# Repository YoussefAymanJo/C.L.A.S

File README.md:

# C.L.A.S

## Description
Is an abbreviation for a closed-loop feedback system.A system that monitors and acts based on lettuce & pepper plant conditions in 6th October city,Egypt.
In  monitors temperature & Humidty & soil moiture & light intensity.then,it responds in case in change in plants optimal range conditonns.As,it used actuctors,peltiers ,humidifier,heating lamp ,grow light , water pump and fan to out excessive humidty.It powered by esp s3.and cloud base storage of firebase,show data at moment on web app.
## Why it was built
This is grade 11 Capstone Project in my school,so i must make it.It is about the challenge Egypt faces in integrating IoT closed systems with farming.My project solve this by providing high nutrition needed crops in my area all the year,lettuce&pepper controlled  by closed feedback system.that control temperature & humidty & soil moisture & light parameters.
## How to use it / Build it
 First of all,prepare materials ,then buy wood and start cut into blocks,after that open parts in wood using cnc for actuactors and other in pcb enclosure.After that assemble all together using nails and wood glue.then adding electronic compontes sesnor & actucators.and connect them first to power supply to test it.then connect each one alone first to esp ,then test them all.after that,check wire isolation and system working and real data from sesnors.test system manul for 2 h. Finally, add plants and soil.
## Schematic
I made symbols & footprints for missing parts in kicad,then wires them ,and add pin headers instead of wire sensor direct to pcb,finally,organize schematic and adding flow diagram of system feedback.

## PCB
pcb consist of pinheaders and will connect to sensors using isolated wires & jumpers,and actuctors will connect to mosfets.I made pcb on kicad,body outline first,the routed componets together.

## CAD
i assembled greenhouse on fusion and make enclosure for pcb ,power supply & buck.

## Firmware
I made esp code and web to monitor data form firebase,but i will add js part later during building
### ESp code 

### website 
https://youssefaymanjo.github.io/WEb-clas/
## BOM 
I made the BOM  and needed materials ,in egypt then convert its price to USD dollar.

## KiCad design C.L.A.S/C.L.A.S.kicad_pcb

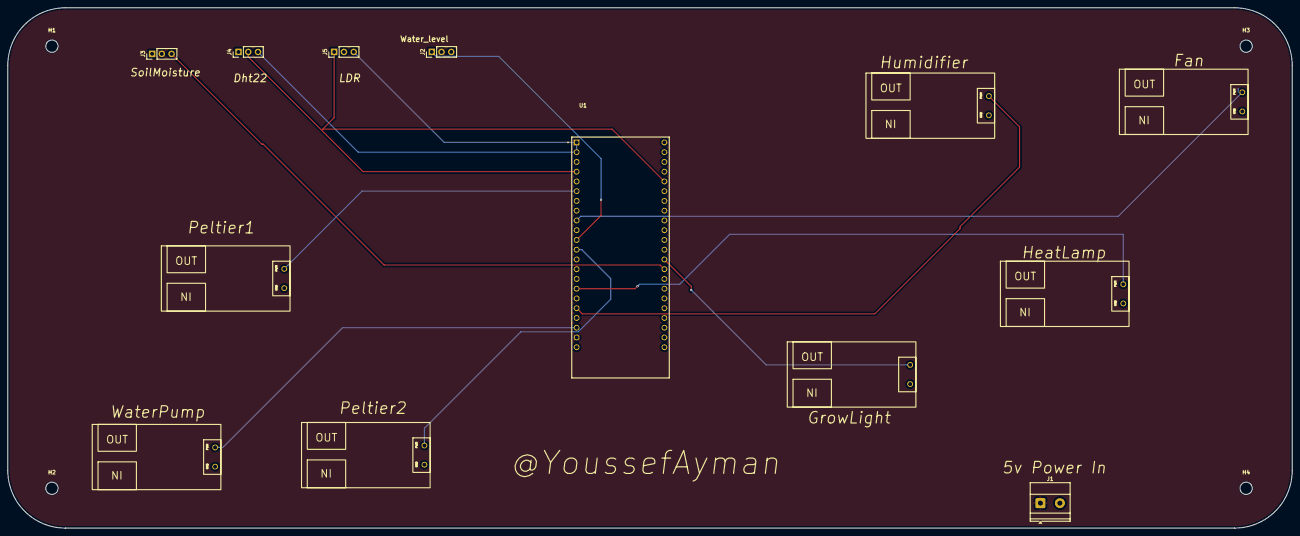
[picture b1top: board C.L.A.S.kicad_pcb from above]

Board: 2 copper layers, 334.5 x 135.5 mm, 17 parts (0 on the bottom side), 14 nets.

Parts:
Fan1: MOSFET_KIT
H1, H2, H3, H4: MountingHole; MountingHole_3.2mm_M3
Heatlamp1: MOSFET_KIT
Humidifer1: MOSFET_KIT
J1: Screw_Terminal_01x02; TerminalBlock_Phoenix_MKDS-1,5-2-5.08_1x02_P5.08mm_Horizont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
J2, J3, J4, J5: Conn_01x03_Pin; PinHeader_1x03_P2.54mm_Vertical
Peltier1: MOSFET_KIT
U1: ESP32-S3-DEVKITC-1-N8R2; XCVR_ESP32-S3-DEVKITC-1-N8R2
Waterpump1, Waterpump2: MOSFET_KIT
peltier2: MOSFET_KIT

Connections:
Dht22: J4.2, U1.J1_4 (GPIO4)
Fan: Fan1.2 (PMW), U1.J1_9 (GPIO16)
GND: Fan1.1 (GND), Heatlamp1.1 (GND), Humidifer1.1 (GND), J1.2, J2.3, J3.1, J4.1, J5.2, Peltier1.1 (GND), U1.J1_22 (GND), U1.J3_1 (GND), U1.J3_21 (GND), U1.J3_22 (GND), Waterpump1.1 (GND), Waterpump2.1 (GND), peltier2.1 (GND)
Heatlamp: Heatlamp1.2 (PMW), U1.J1_16 (GPIO10)
Humidifier: Humidifer1.2 (PMW), U1.J1_18 (GPIO12)
LDR: J5.1, U1.J3_5 (GPIO2)
Peltier1: Peltier1.2 (PMW), U1.J1_6 (GPIO6)
Peltier2: U1.J1_12 (GPIO8), peltier2.2 (PMW)
Soil: J3.3, U1.J3_14 (GPIO0)
VCC: J1.1, J2.2, J3.2, U1.J1_21 (5V0)
VCC_3v: J4.3, J5.3, U1.J1_1 (3V3), U1.J1_2 (3V3)
Water_level: J2.1, U1.J1_11 (GPIO18)
Waterpump: U1.J1_20 (GPIO14), Waterpump1.2 (PMW)
grow: U1.J3_13 (GPIO35), Waterpump2.2 (PMW)

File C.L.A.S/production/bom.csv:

Designator,Footprint,Quantity,Value,LCSC Part #
"FAN1, HEATLAMP1, HUMIDIFER1, PELTIER1, PELTIER2, WATERPUMP1, WATERPUMP2",MOSFET_KIT,7,~,
J1,"TerminalBlock_Phoenix_MKDS-1,5-2-5.08_1x02_P5.08mm_Horizontal",1,Screw_Terminal_01x02,
"J2, J3, J4, J5",PinHeader_1x03_P2.54mm_Vertical,4,Conn_01x03_Pin,
U1,XCVR_ESP32-S3-DEVKITC-1-N8R2,1,ESP32-S3-DEVKITC-1-N8R2,

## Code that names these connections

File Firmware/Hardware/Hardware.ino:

// libraries importing
#include "DHT.h"
#include <WiFi.h>
#include <Firebase_ESP_Client.h>
#include "addons/TokenHelper.h"
#include "addons/RTDBHelper.h"

// firebase realtime
#define WIFI_SSID "***********"
#define WIFI_PASSWORD "*************"
#define FIREBASE_URL "https://console.firebase.google.com/project/clas-59589/database/clas-59589-default-rtdb/data"
#define FIREBASE_SECRET "**************"

// sensors definition
#define DHTPIN 4
#define DHTTYPE DHT22
#define LDR_pin 2
#define Soil_pin 0
#define water_level_pin 18

// power controllers definition
#define peltier1 6
#define peltier2 8
#define heatlamp 10
#define Humidifier 12
#define waterpump 14
#define fan_h 16
#define growlight 35
// var ranges
struct ranges
{
  int templow;
  int temphigh;
  int humidlow;
  int humidhigh;
  int soillow;
  int soilhigh;
  int lightlow;
  int lighthigh;
}
// lettuce
const ranges lettuce = {
    15, 24,
    60, 80,
    2100, 1400,
    1500, 700};
// pepper
const ranges pepper = {
    20, 30,
    55, 75,
    2100, 1400,
    1500, 700};

DHT dht(DHTPIN, DHTTYPE);
// firebase
FirebaseData fbdo;
FirebaseAuth auth;
FirebaseConfig config;
unsigned long sendDataPrevMillis = 0;
// status actuctors
int pel1 = 0, pel2 = 0, fan = 0, lamp = 0, light = 0, humid = 0, pump = 0;
void setup()
{
  Serial.begin(115200);
  dht.begin();
  pinMode(LDR_pin, INPUT);
  pinMode(Soil_pin, INPUT);
  PinMode(water_level_pin, INPUT);
  PinMode(peltier1, OUTPUT);
  PinMode(peltier2, OUTPUT);
  PinMode(heatlamp, OUTPUT);
  pinMode(Humidifier, OUTPUT);
  pinMode(waterpump, OUTPUT);
  pinMode(fan_h, OUTPUT);
  pinMode(growlight, OUTPUT);
  // wifi connection
  Wifi.begin(WIFI_SSID, WIFI_PASSWORD);
  while (WiFi.status() != WL_CONNECTED)
  {
    delay(300);
    Serial.print(".");
  }
  config.database_url = FIREBASE_URL;
  config.signer.tokens.legacy_token = FIREBASE_SECRET;
  Firebase.begin(&config, &auth);
  Firebase.reconnectWiFi(true);
  delay(5000);
}

void loop()
{
  // plant type
  int planttype = 0;
  if (Firebase.RTDB.getInt(&fbdo, "/greenhouse/plant_type"))
  {
      planttype = fbdo.intData();
  }
  double temperature = dht.readTemperature();
  double Humidty = dht.readHumidty();
  int light = analogRead(LDR_pin);
  float soilmoisture = analogRead(Soil_pin);
  int waterlevel = analogRead(water_level_pin);
  float waterprecent = (waterlevel / 4095.0) * 100;

  serial.print("Temperature :")
  serial.print(temperature);
  serial.print("Celsuis / Humidty : ");
  serial.print(" % / Soil Moisture : ");
  serial.print(soilmoisture);
  serial.print(" % / Light Amount : ");
  serial.print(light);
  serial.print(" % / Water level : ");
  serial.print(waterlevel);
  serial.print(" % ");
  if (planttype == 0)
  {
    // temperature
    if (temperature > lettuce.temphigh)
    {
      analogWrite(peltier1, 255);
      analogWrite(peltier2, 255);
      analogWrite(heatlamp, 0);
      pel1 = 1, pel 2 = 1, lamp = 0;
    }
    else if (temperature < lettuce.templow)
    {
      analogWrite(peltier1, 0);
      analogWrite(peltier2, 0);
      analogWrite(heatlamp, 255);
      pel1 = 0, pel 2 = 0, lamp = 1;
    }
    else
    {
      analogWrite(peltier1, 0);
      analogWrite(peltier2, 0);
      analogWrite(heatlamp, 0);
      pel1 = 0, pel 2 = 0, lamp = 0;
    }
    // Humidty
    if (Humidty > lettuce.humidhigh)
    {
      analogWrite(Humidifier, 0);
      analogWrite(fan, 255);
      humid = 0, fan = 1;
    }
    else if (Humidty < lettuce.humidlow)
    {
      analogWrite(fan, 0);
      analogWrite(Humidifier, 255);
      humid = 1, fan = 0;
    }
    else
    {
      analogWrite(fan, 0);
      analogWrite(Humidifier, 0);
      humid = 0, fan = 0;
    }
    // Soil
    if (soilmoisture > lettuce.soilhigh)
    {
      analogWrite(waterpump, 0);
      pump = 0;
    }
    else if (temperature < lettuce.soillow)
    {
      analogWrite(waterpump, 255);
      pump = 1;
    }
    else
    {
      analogWrite(waterpump, 0);
      pump = 0;
    }
    // Light
    if (light > lettuce.lighthigh)
    {
      analogWrite(growlight, 255);
      light = 1;
    }
    else if (light < lettuce.lightlow)
    {
      analogWrite(growlight, 0);
      light = 0;
    }
    else
    {
      analogWrite(growlight, 0);
      light = 0;
    }
  }
  else if (planttype == 1)
  {
    // temperature
    if (temperature > pepper.temphigh)
    {
      analogWrite(peltier1, 255);
      analogWrite(peltier2, 255);
      analogWrite(heatlamp, 0);
      pel1 = 1, pel 2 = 1, lamp = 0;
    }
    else if (temperature < pepper.templow)
    {
      analogWrite(peltier1, 0);
      analogWrite(peltier2, 0);
      analogWrite(heatlamp, 255);
      pel1 = 0, pel 2 = 0, lamp = 0;
    }
    else
    {
      analogWrite(peltier1, 0);
      analogWrite(peltier2, 0);
      analogWrite(heatlamp, 0);
      pel1 = 0, pel 2 = 0, lamp = 0;
    }
    // Humidty
    if (Humidty > pepper.humidhigh)
    {
      analogWrite(Humidifier, 0);
      analogWrite(fan, 255);
      humid = 0, fan = 1;
    }
    else if (Humidty < pepper.humidlow)
    {
      analogWrite(fan, 0);
      analogWrite(Humidifier, 255);
      humid = 1, fan = 0;
    }
    else
    {
      analogWrite(fan, 0);
      analogWrite(Humidifier, 0);
      humid = 0, fan = 0;
    }
    // Soil
    if (soilmoisture > pepper.soilhigh)
    {
      analogWrite(waterpump, 0);
      pump = 0;
    }
    else if (temperature < pepper.soillow)
    {
      analogWrite(waterpump, 255);
      pump = 1;
    }
    else
    {
      analogWrite(waterpump, 0);
      pump = 0;
    }
    // Light
    if (light > pepper.lighthigh)
    {
      analogWrite(growlight, 255);
      light = 1;
    }
    else if (light < pepper.lightlow)
    {
      analogWrite(growlight, 0);
      light = 0;
    }
    else
    {
      analogWrite(growlight, 0);
      light = 0;
    }
  }
  else
  {
    // manual mode
    String controlBase = "/gardenConfig/actuators/";
    if (Firebase.RTDB.getBool(&fbdo, controlBase + "peltier1"))
      analogWrite(peltier1, fbdo.boolData() ? 255 : 0);
    if (Firebase.RTDB.getBool(&fbdo, controlBase + "peltier2"))
      analogWrite(peltier2, fbdo.boolData() ? 255 : 0);
    if (Firebase.RTDB.getBool(&fbdo, controlBase + "heatlamp"))
      analogWrite(heatlamp, fbdo.boolData() ? 255 : 0);
    if (Firebase.RTDB.getBool(&fbdo, controlBase + "humidifier"))
      analogWrite(humidifier, fbdo.boolData() ? 255 : 0);
    if (Firebase.RTDB.getBool(&fbdo, controlBase + "waterpump"))
      analogWrite(waterpump, fbdo.boolData() ? 255 : 0);
    if (Firebase.RTDB.getBool(&fbdo, controlBase + "fan"))
      analogWrite(fan, fbdo.boolData() ? 255 : 0);
    if (Firebase.RTDB.getBool(&fbdo, controlBase + "growlight"))
      analogWrite(growlight, fbdo.boolData() ? 255 : 0);
  }
  // update firebase
  FirebaseJson updateData;
  updateData.set("sensors/temperature", temperature);
  updateData.set("sensors/humidity", humidity);
  updateData.set("sensors/light", light);
  updateData.set("sensors/soil_moisture", soilmoisture);
  updateData.set("sensors/water_level", waterlevel);
  updateData.set("sensors/water_percent", waterpercent);

  if (planttype != 3)
  {
    updateData.set("actuators/peltier1", pel1);
    updateData.set("actuators/peltier2", pel2);
    updateData.set("actuators/heatlamp", lamp);
    updateData.set("actuators/humidifier", humid);
    updateData.set("actuators/waterpump", pump);
    updateData.set("actuators/fan", fan);
    updateData.set("actuators/growlight", light);
  }
  if (Firebase.RTDB.updateNode(&fbdo, "/greenhouse", &updateData))
  {
    Serial.println("Firebase updated successfully.");
  }
  else
  {
    Serial.println("Firebase update failed: " + fbdo.errorReason());
  }

  delay(30000);
}
